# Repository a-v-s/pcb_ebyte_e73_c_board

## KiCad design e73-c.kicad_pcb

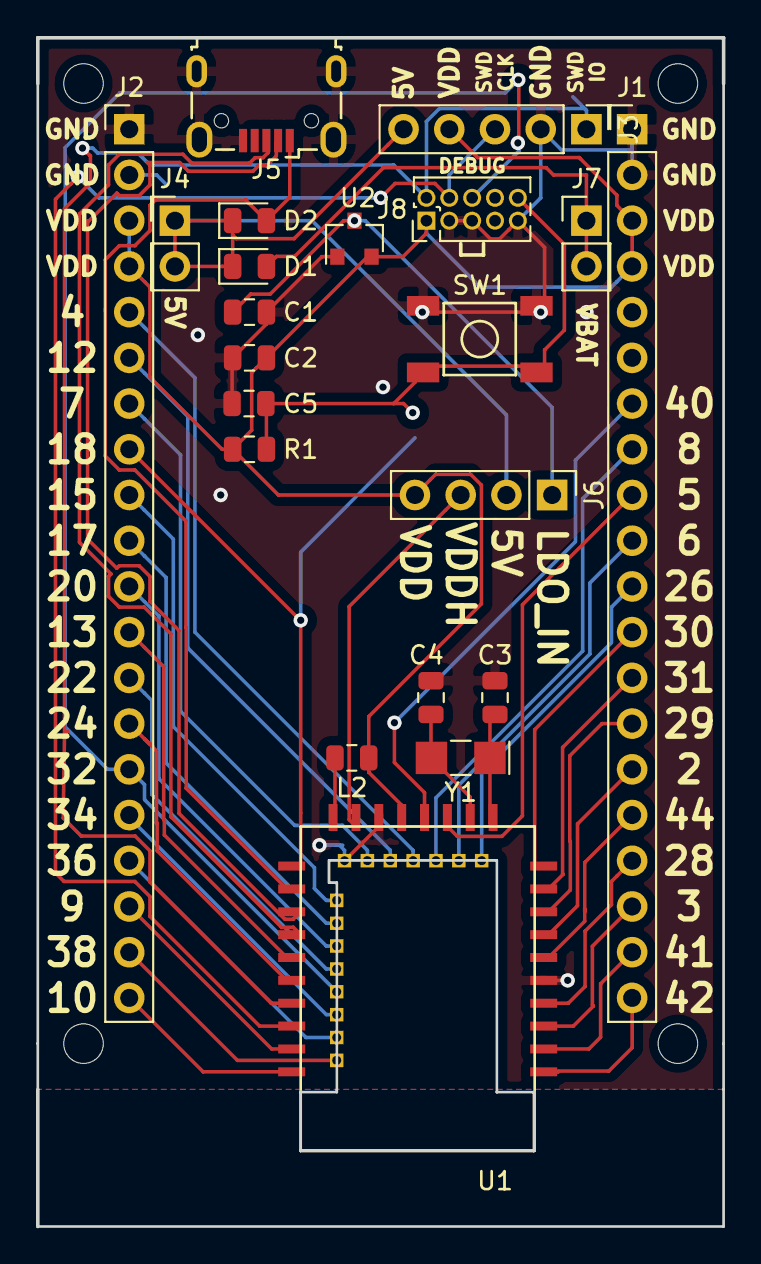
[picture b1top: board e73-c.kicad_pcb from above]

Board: 2 copper layers, 38.1 x 66.0 mm, 26 parts (1 on the bottom side), 45 nets.

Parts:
C1: 1u; C_0805_2012Metric
C2: 2u2; C_0805_2012Metric
C3, C4, C5: C_Small; C_0805_2012Metric
D1, D2: D_Zener; D_0805_2012Metric
H1, H2, H3, H4: MountingHole; MountingHole_2.2mm_M2_ISO7380
J1, J2: Conn_01x20_Male; PinHeader_1x20_P2.54mm_Vertical
J3: Conn_01x04_Male; PinHeader_1x05_P2.54mm_Vertical
J4, J7: Conn_01x02; PinHeader_1x02_P2.54mm_Vertical
J5: USB_B_Micro; USB_Micro-B_Wuerth_629105150521
J6: Conn_02x03_Odd_Even; PinHeader_1x04_P2.54mm_Vertical
J8: Conn_02x05_Odd_Even; PinHeader_2x05_P1.27mm_Vertical
JP3: SolderJumper_2_Bridged; SolderJumper-2_P1.3mm_Bridged_RoundedPad1.0x1.5mm
L2: 10u; L_0805_2012Metric
R1: 10K; R_0805_2012Metric
SW1: SW_Push; TS-1187
U1: E73-C; E73-C-CH
U2: MCP1700-3302E_SOT23; SOT-23
Y1: Crystal; Crystal_SMD_MicroCrystal_CC7V-T1A-2Pin_3.2x1.5mm_HandSolder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

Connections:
2: J1.15, U1.7
3: J1.18, U1.3
4: J2.5, U1.18
5: J1.9, U1.15
5V: D1.1, D2.1, J3.5, J4.1, J4.2, J6.2
6: J1.10, U1.14
7: J2.7, U1.22
8: J1.8, U1.16
9: J2.18, U1.41
10: J2.20, U1.43
12: J2.6, U1.20
13: J2.12, U1.33
15: J2.9, U1.28
17: J2.10, U1.30
18: J2.8, JP3.2, U1.26
20: J2.11, U1.32
22: J2.13, U1.34
24: J2.14, U1.35
26: J1.11, U1.12
28: J1.17, U1.4
29: J1.14, U1.8
30: J1.12, U1.10
31: J1.13, U1.9
32: J2.15, J8.6, U1.36
34: J2.16, U1.38
36: J2.17, U1.40
38: J2.19, U1.42
40: J1.7, U1.17
41: J1.19, U1.2
42: J1.20, U1.1
44: J1.16, U1.6
!RST: C5.2, J8.10, JP3.1, R1.2, SW1.1
D+: J5.3, U1.31
D-: J5.2, U1.29
GND: C1.2, C2.2, C3.2, C4.2, C5.1, J1.1, J1.2, J2.1, J2.2, J3.2, J5.5, J5.6, J8.3, J8.5, J8.9, SW1.2, U1.5, U1.21, U1.24, U2.1
LDO_IN: C1.1, J6.1, U2.3
unnamed: L2.2, U1.25
SWDCLK: J3.3, J8.4, U1.39
SWDIO: J3.1, J8.2, U1.37
VBAT: D1.2, J7.1, J7.2
VBUS: D2.2, J5.1, U1.27
VDD: C2.1, J1.3, J1.4, J2.3, J2.4, J3.4, J6.4, J8.1, L2.1, R1.1, U1.19, U2.2
VDDH: J6.3, U1.23
XL1: C3.1, U1.11, Y1.1
XL2: C4.1, U1.13, Y1.2

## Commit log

2018-12-05 Switch to smaller (SOT23) LDO, SolderJumper in stead of Jumpers for LFXTAL
2018-12-15 Redesign V3 WIP
2018-12-16 Re-arrange labels for V3
2018-12-26 Updated footprint + routed v3
2019-01-03 E73-C-V3
2020-01-04 Gerber
2021-05-24 Fix pin labels + add E module
2021-05-24 Fix module hole
